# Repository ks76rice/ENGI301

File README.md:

# ENGI301
Repository for ENGI301 course work.

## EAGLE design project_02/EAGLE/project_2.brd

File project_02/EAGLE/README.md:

This folder contains EAGLE files (schematics, layout, and library) for a PCB for a USB Music Player.

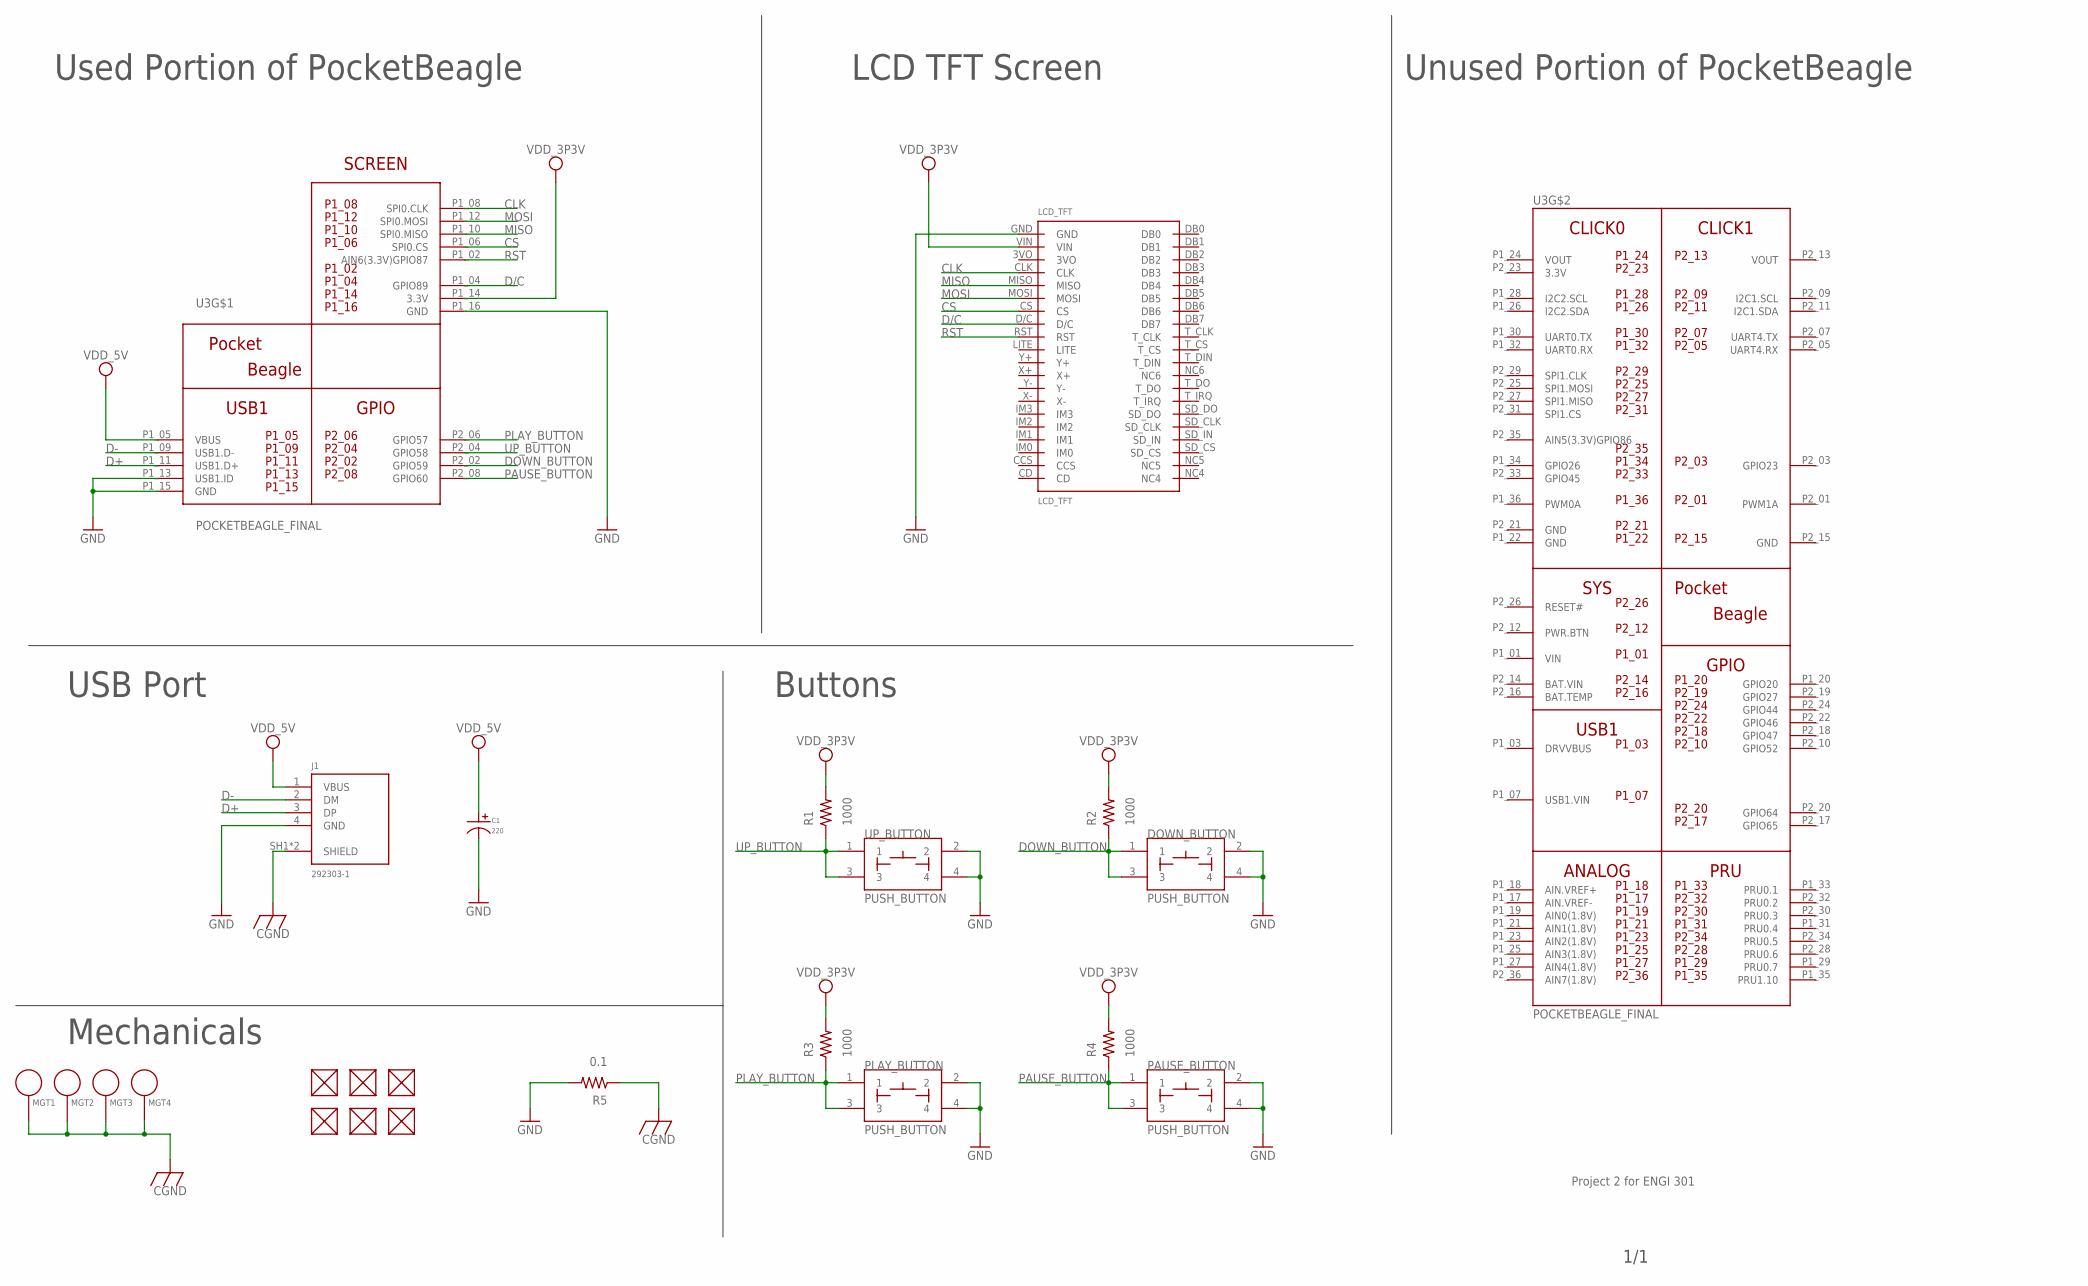
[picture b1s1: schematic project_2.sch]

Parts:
C1: 220; CP10MM
DOWN_BUTTON: PUSH_BUTTON; BUTTON_12.5MM
FUD1, FUD2, FUD3, FUD4, FUD5, FUD6: FIDUCIAL; FIDUCIAL_40MIL
J1: 292303-1; TE_292303-1
LCD_TFT: LCD_TFT
MGT1, MGT2, MGT3, MGT4: MOUNTING_HOLE
PAUSE_BUTTON: PUSH_BUTTON; BUTTON_12.5MM
PLAY_BUTTON: PUSH_BUTTON; BUTTON_12.5MM
R1, R2, R3, R4: 1000; R0603
R5: 0.1; R0603
U3: POCKETBEAGLE_FINAL; POCKETBEAGLE
UP_BUTTON: PUSH_BUTTON; BUTTON_12.5MM

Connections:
3.3V: U3.P2_23 (3.3V)
BAT.VIN: U3.P2_14 (BAT.VIN)
CGND: J1.SH1 (SHIELD), J1.SH2 (SHIELD), MGT1.P$1, MGT2.P$1, MGT3.P$1, MGT4.P$1, R5.1
CLK: LCD_TFT.CLK, U3.P1_08 (SPI0.CLK)
CS: LCD_TFT.CS, U3.P1_06 (SPI0.CS)
D+: J1.3 (DP), U3.P1_11 (USB1.D+)
D-: J1.2 (DM), U3.P1_09 (USB1.D-)
D/C: LCD_TFT.D/C, U3.P1_04 (GPIO89)
DOWN_BUTTON: DOWN_BUTTON.1, DOWN_BUTTON.3, R2.1, U3.P2_02 (GPIO59)
GND: C1.P$2, DOWN_BUTTON.2, DOWN_BUTTON.4, J1.4 (GND), LCD_TFT.GND, PAUSE_BUTTON.2, PAUSE_BUTTON.4, PLAY_BUTTON.2, PLAY_BUTTON.4, R5.2, U3.P1_13 (USB1.ID), U3.P1_15 (GND), U3.P1_16 (GND), U3.P1_22 (GND), U3.P2_15 (GND), U3.P2_21 (GND), UP_BUTTON.2, UP_BUTTON.4
MISO: LCD_TFT.MISO, U3.P1_10 (SPI0.MISO)
MOSI: LCD_TFT.MOSI, U3.P1_12 (SPI0.MOSI)
PAUSE_BUTTON: PAUSE_BUTTON.1, PAUSE_BUTTON.3, R4.1, U3.P2_08 (GPIO60)
PLAY_BUTTON: PLAY_BUTTON.1, PLAY_BUTTON.3, R3.1, U3.P2_06 (GPIO57)
RST: LCD_TFT.RST, U3.P1_02 (AIN6(3.3V)GPIO87)
UP_BUTTON: R1.1, U3.P2_04 (GPIO58), UP_BUTTON.1, UP_BUTTON.3
VDD_3P3V: LCD_TFT.VIN, R1.2, R2.2, R3.2, R4.2, U3.P1_14 (3.3V)
VDD_5V: C1.P$1, J1.1 (VBUS), U3.P1_05 (VBUS)
VIN: U3.P1_01 (VIN)
VOUT: U3.P1_24 (VOUT), U3.P2_13 (VOUT)

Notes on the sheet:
Unused Portion of PocketBeagle
Used Portion of PocketBeagle
LCD TFT Screen
Buttons
1/1
POCKETBEAGLE_FINAL
Project 2 for ENGI 301
USB Port
Mechanicals

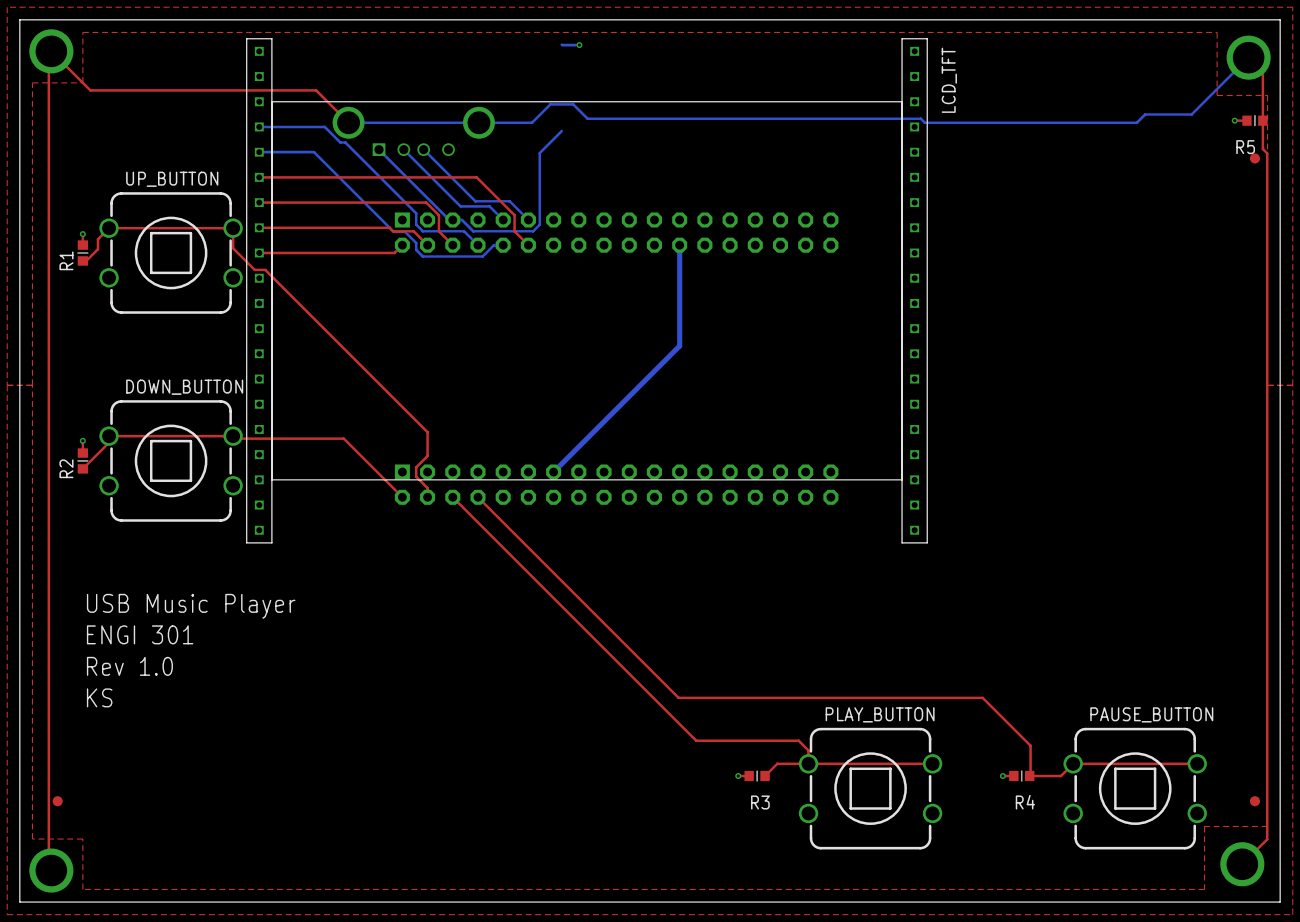
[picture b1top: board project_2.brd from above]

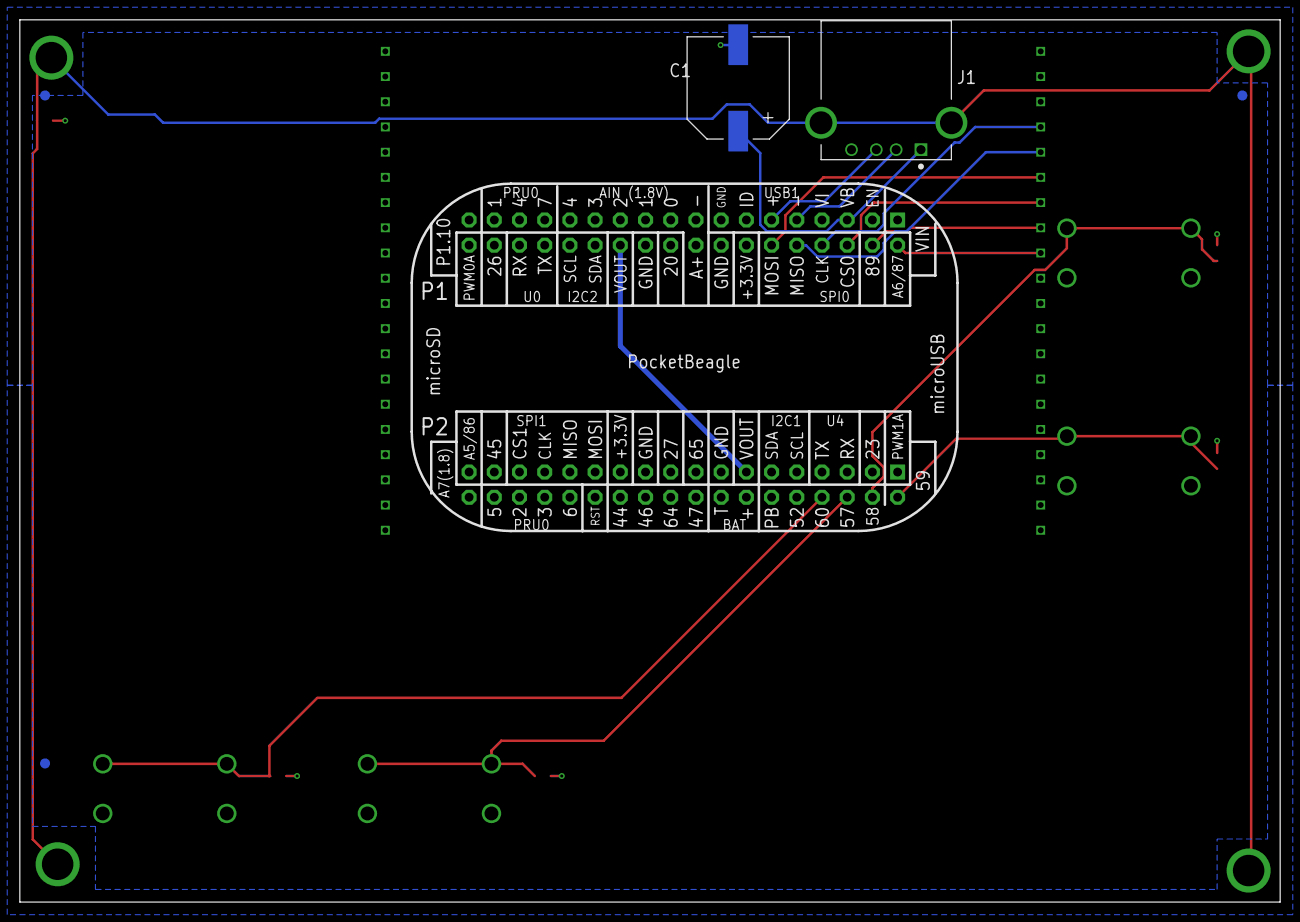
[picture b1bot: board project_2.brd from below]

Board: 4 copper layers, 127.0 x 88.9 mm, 23 parts (6 on the bottom side), 17 nets.

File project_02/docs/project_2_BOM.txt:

Partlist exported from C:/Users/SunKe/Downloads/project_2_final/project_2.sch at 12/14/2021 6:13 PM

Qty Value              Device             Package        Parts                                             Description                                    CENTERLINE_PITCH COMMENT  DESCRIPTION DIGI-KEY_PART_NUMBER EU_ROHS_COMPLIANCE HOUSEPART MF   MP     MPN     NUMBER_OF_POSITIONS PACKAGE POPULATE          PRODUCT_TYPE PURCHASE-URL TOLERANCE URL             VOLTAGE 
1   0.1                R_R0603            R0603          R5                                                RESISTOR, American symbol                                                                                                                                                                                                                                            
4   1000               R_R0603            R0603          R1, R2, R3, R4                                    RESISTOR, American symbol                                                                                                                                                                                                                                            
1   220                CAPACITOR_P_10MM   CP10MM         C1                                                Library:  MF_Passives                                                                                                                                                                  1                                                                             
1   292303-1           292303-1           TE_292303-1    J1                                                CONN USB RECEPT R/A TYPE A 4POS                2 mm[.078 in]    292303-1  Conn        Data                 USB                Recept    2.0  4 Pos  1 Port  Rt Angle            A Ser   Tin over Copper  A31726-ND    Compliant              TE Connectivity 292303-1
6   FIDUCIAL           FIDUCIAL           FIDUCIAL_40MIL FUD1, FUD2, FUD3, FUD4, FUD5, FUD6                                                                                                                                                                                                                                                                                     
1   LCD_TFT            LCD_TFT            LCD_TFT        LCD_TFT                                           TFT LCD IL9341 by Adafruit                                                                                                                                                                                                                                                                     
4   MOUNTING_HOLE      MOUNTING_HOLE      MOUNTING_HOLE  MGT1, MGT2, MGT3, MGT4                            Chassis Mounting Hole w/GND connection ability                                                                                                                                                                                                                       
1   POCKETBEAGLE_FINAL POCKETBEAGLE_FINAL POCKETBEAGLE   U3                                                PocketBeagle by Octavo Systems                                                                                                                                                                                                                                                                     
4   PUSH_BUTTON        PUSH_BUTTON        BUTTON_12.5MM  DOWN_BUTTON, PAUSE_BUTTON, PLAY_BUTTON, UP_BUTTON

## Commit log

2021-09-17 Update README.md
    Updating README.md
2021-10-05 Create simple_calc
2021-10-05 Update simple_calc
2021-10-17 Create Notes
2021-12-15 Add files via upload
    Adding screenshots of the top and bottom PCB
2021-12-15 Add files via upload
    PDF of the schematic
